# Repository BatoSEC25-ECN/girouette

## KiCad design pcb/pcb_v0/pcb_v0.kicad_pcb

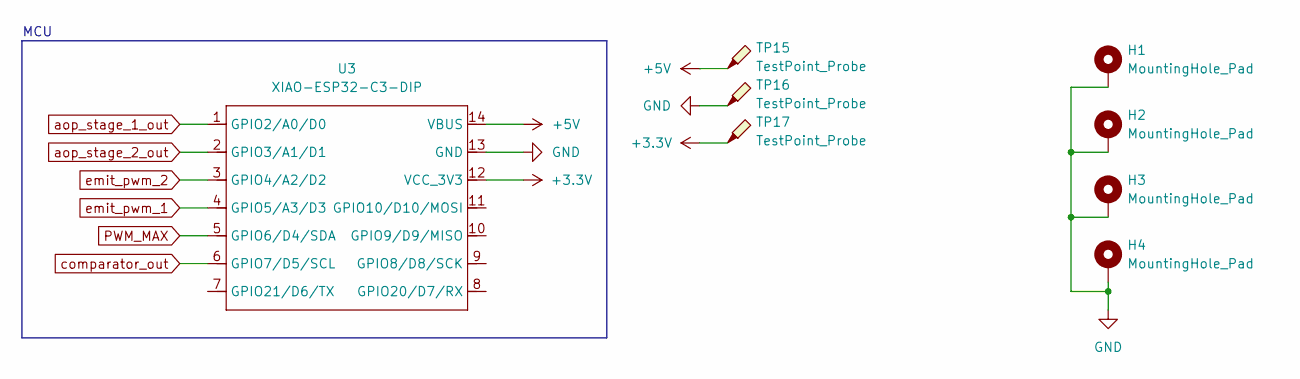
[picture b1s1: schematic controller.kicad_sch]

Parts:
H1, H2, H3, H4: MountingHole_Pad; MountingHole_2.2mm_M2_Pad_TopBottom
TP15, TP16, TP17: TestPoint_Probe; TestPoint_THTPad_3.0x3.0mm_Drill1.5mm
U3: XIAO-ESP32-C3-DIP; XIAO-ESP32C3-DIP

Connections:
+3.3V: TP17.1, U3.12 (VCC_3V3); also elsewhere on the board
+5V: TP15.1, U3.14 (VBUS); also elsewhere on the board
GND: H1.1, H2.1, H3.1, H4.1, TP16.1, U3.13 (GND); also elsewhere on the board
PWM_MAX: U3.5 (GPIO6/D4/SDA); also elsewhere on the board
aop_stage_1_out: U3.1 (GPIO2/A0/D0); also elsewhere on the board
aop_stage_2_out: U3.2 (GPIO3/A1/D1); also elsewhere on the board
comparator_out: U3.6 (GPIO7/D5/SCL); also elsewhere on the board
emit_pwm_1: U3.4 (GPIO5/A3/D3); also elsewhere on the board
emit_pwm_2: U3.3 (GPIO4/A2/D2); also elsewhere on the board

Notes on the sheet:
MCU

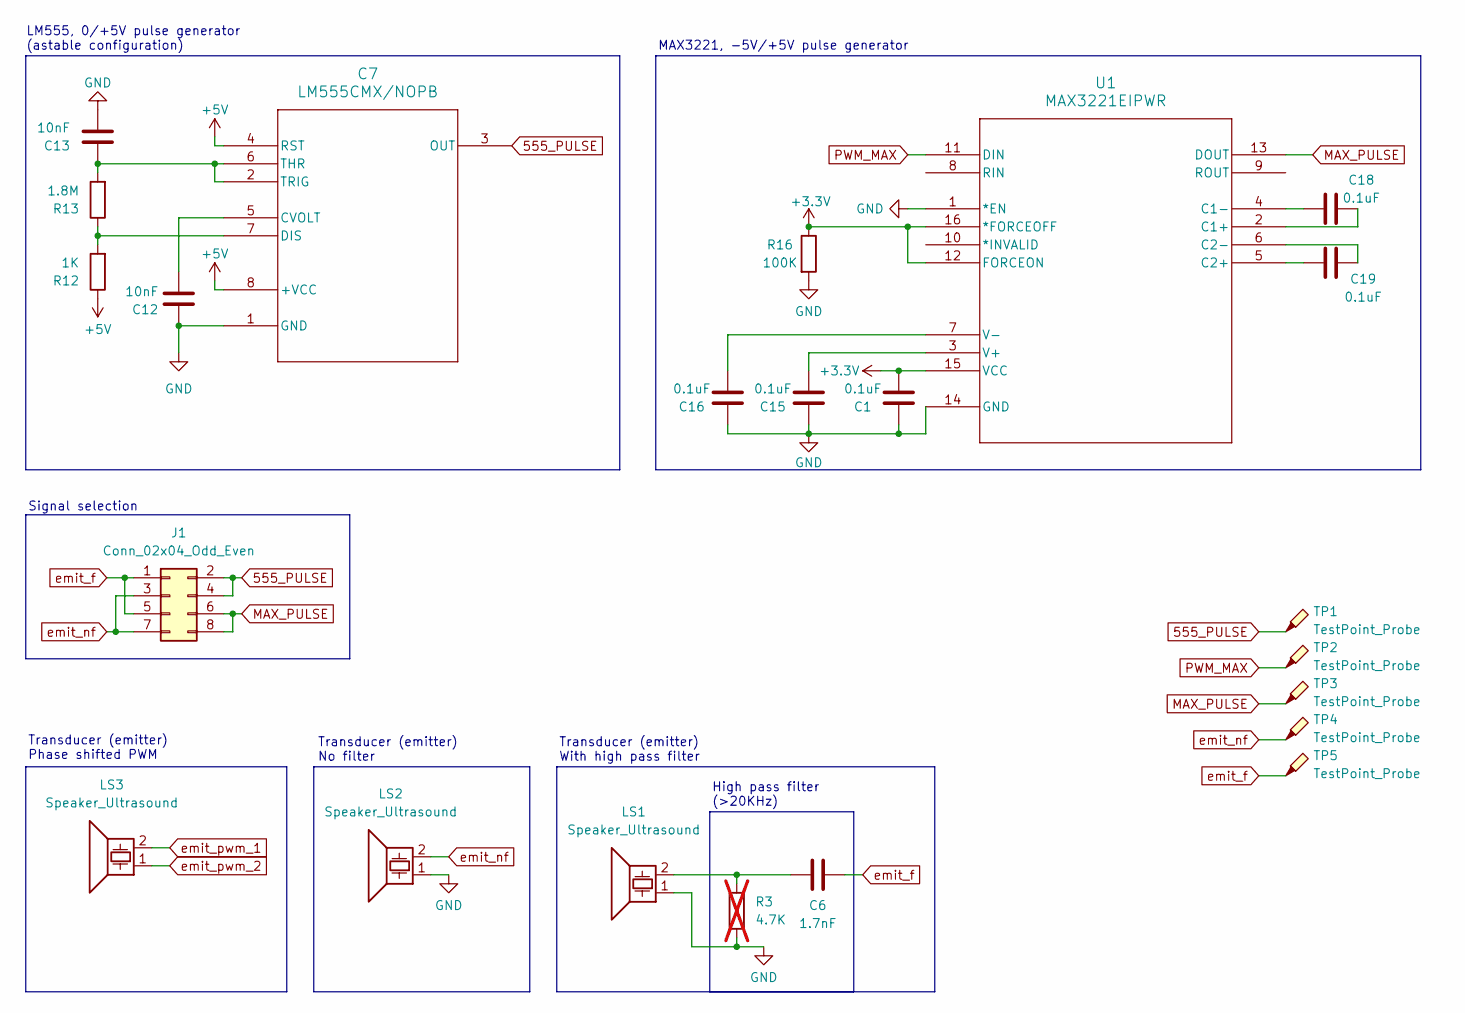
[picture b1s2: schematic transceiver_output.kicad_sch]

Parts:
C1, C15, C16, C18, C19: 0.1uF; C_Disc_D4.3mm_W1.9mm_P5.00mm
C6: 1.7nF; C_Disc_D4.3mm_W1.9mm_P5.00mm
C7: LM555CMX/NOPB; M08A-M
C12, C13: 10nF; C_Disc_D4.3mm_W1.9mm_P5.00mm
J1: Conn_02x04_Odd_Even; PinHeader_2x04_P2.54mm_Vertical
LS1, LS2, LS3: Speaker_Ultrasound; PinHeader_1x02_P2.54mm_Vertical
R3: 4.7K; R_Axial_DIN0207_L6.3mm_D2.5mm_P10.16mm_Horizontal; not fitted
R12: 1K; R_Axial_DIN0207_L6.3mm_D2.5mm_P10.16mm_Horizontal
R13: 1.8M; R_Axial_DIN0207_L6.3mm_D2.5mm_P10.16mm_Horizontal
R16: 100K; R_Axial_DIN0207_L6.3mm_D2.5mm_P10.16mm_Horizontal
TP1, TP2, TP3, TP4, TP5: TestPoint_Probe; TestPoint_THTPad_3.0x3.0mm_Drill1.5mm
U1: MAX3221EIPWR; PW16-M

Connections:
555_PULSE: C7.3 (OUT), J1.2, J1.4, TP1.1
+3.3V: C1.2, R16.1, U1.12 (FORCEON), U1.15 (VCC), U1.16 (*FORCEOFF); also elsewhere on the board
+5V: C7.4 (RST), C7.8 (+VCC), R12.1; also elsewhere on the board
GND: C1.1, C7.1 (GND), C12.1, C13.2, C15.1, C16.1, LS1.1, LS2.1, R3.2, R16.2, U1.1 (*EN), U1.14 (GND); also elsewhere on the board
MAX_PULSE: J1.6, J1.8, TP3.1, U1.13 (DOUT)
unnamed: C6.1, LS1.2, R3.1
unnamed: C7.5 (CVOLT), C12.2
unnamed: C7.7 (DIS), R12.2, R13.1
unnamed: C7.2 (TRIG), C7.6 (THR), C13.1, R13.2
unnamed: C18.2, U1.2 (C1+)
unnamed: C18.1, U1.4 (C1-)
unnamed: C19.1, U1.5 (C2+)
unnamed: C19.2, U1.6 (C2-)
unnamed: C15.2, U1.3 (V+)
unnamed: C16.2, U1.7 (V-)
PWM_MAX: TP2.1, U1.11 (DIN); also elsewhere on the board
emit_f: C6.2, J1.1, J1.5, TP5.1
emit_nf: J1.3, J1.7, LS2.2, TP4.1
emit_pwm_1: LS3.2; also elsewhere on the board
emit_pwm_2: LS3.1; also elsewhere on the board

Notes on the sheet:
Transducer (emitter) No filter
Signal selection
LM555, 0/+5V pulse generator (astable configuration)
MAX3221, -5V/+5V pulse generator
High pass filter (>20KHz)
Transducer (emitter) Phase shifted PWM
Transducer (emitter) With high pass filter

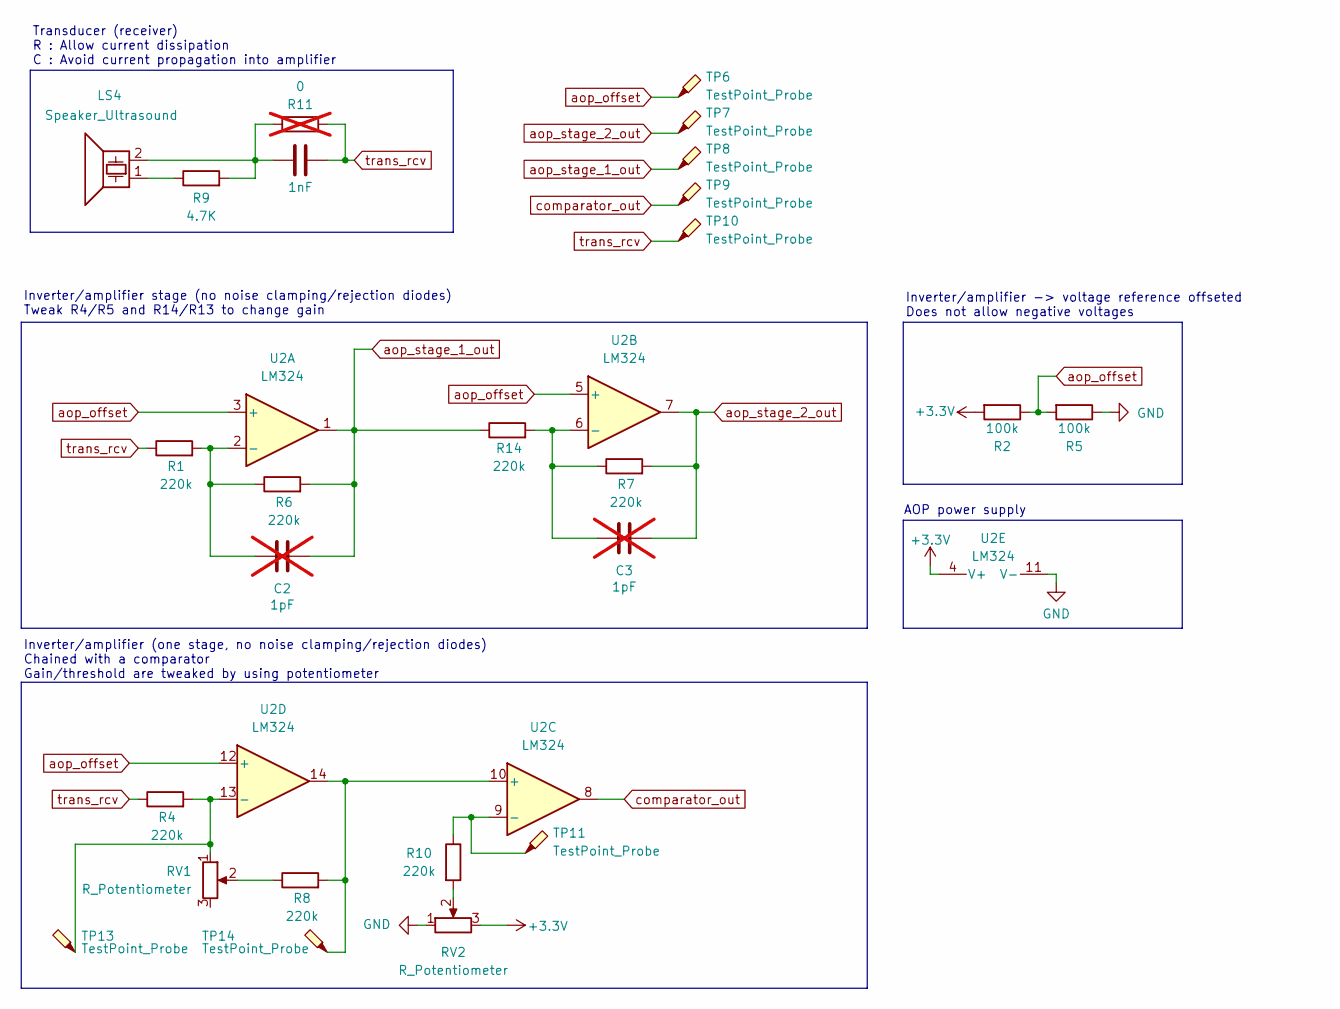
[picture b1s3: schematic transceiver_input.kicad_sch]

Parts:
C2, C3: 1pF; C_Disc_D4.3mm_W1.9mm_P5.00mm; not fitted
C10: 1nF; C_Disc_D4.3mm_W1.9mm_P5.00mm
LS4: Speaker_Ultrasound; PinHeader_1x02_P2.54mm_Vertical
R1, R4, R6, R7, R8, R10, R14: 220k; R_Axial_DIN0207_L6.3mm_D2.5mm_P10.16mm_Horizontal
R2, R5: 100k; R_Axial_DIN0207_L6.3mm_D2.5mm_P10.16mm_Horizontal
R9: 4.7K; R_Axial_DIN0207_L6.3mm_D2.5mm_P10.16mm_Horizontal
R11: 0; R_Axial_DIN0207_L6.3mm_D2.5mm_P10.16mm_Horizontal; not fitted
RV1, RV2: R_Potentiometer; Potentiometer_Bourns_PTV09A-1_Single_Vertical
TP6, TP7, TP8, TP9, TP10, TP11, TP13, TP14: TestPoint_Probe; TestPoint_THTPad_3.0x3.0mm_Drill1.5mm
U2: LM324; N14

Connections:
+3.3V: R2.2, RV2.3, U2.4 (V+); also elsewhere on the board
GND: R5.1, RV2.1, U2.11 (V-); also elsewhere on the board
unnamed: C10.1, LS4.2, R9.2, R11.2
unnamed: LS4.1, R9.1
unnamed: R8.1, RV1.2
unnamed: R10.2, RV2.2
unnamed: C2.2, R1.2, R6.1, U2.2 (-)
unnamed: C3.2, R7.1, R14.2, U2.6 (-)
unnamed: R8.2, TP14.1, U2.10 (+), U2.14
unnamed: R10.1, TP11.1, U2.9 (-)
unnamed: R4.2, RV1.1, TP13.1, U2.13 (-)
aop_offset: R2.1, R5.2, TP6.1, U2.3 (+), U2.5 (+), U2.12 (+)
aop_stage_1_out: C2.1, R6.2, R14.1, TP8.1, U2.1; also elsewhere on the board
aop_stage_2_out: C3.1, R7.2, TP7.1, U2.7; also elsewhere on the board
comparator_out: TP9.1, U2.8; also elsewhere on the board
trans_rcv: C10.2, R1.1, R4.1, R11.1, TP10.1

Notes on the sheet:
Inverter/amplifier -> voltage reference offseted Does not allow negative voltages
Inverter/amplifier (one stage, no noise clamping/rejection diodes) Chained with a comparator Gain/threshold are tweaked by using potentiometer
AOP power supply
Inverter/amplifier stage (no noise clamping/rejection diodes) Tweak R4/R5 and R14/R13 to change gain
Transducer (receiver) R : Allow current dissipation C : Avoid current propagation into amplifier

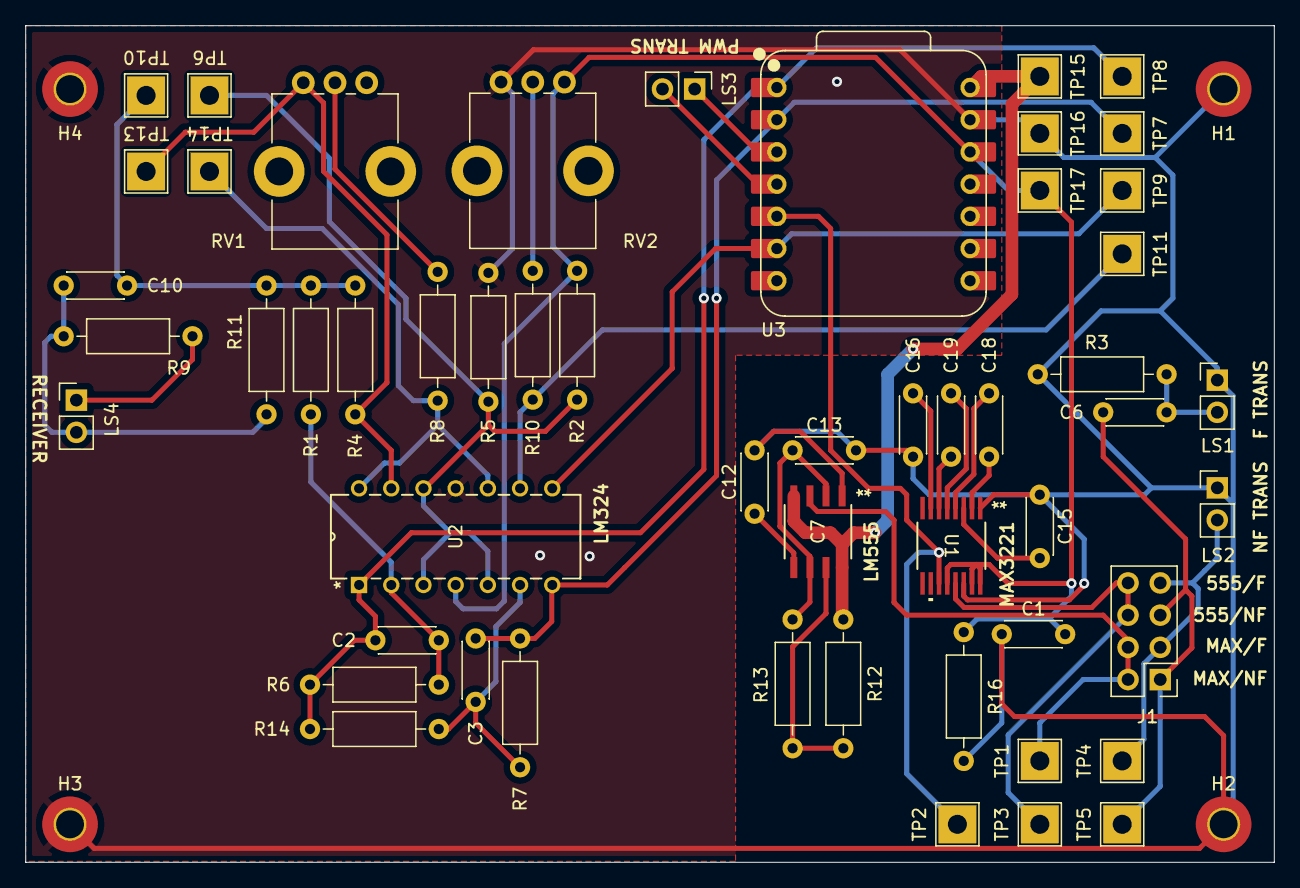
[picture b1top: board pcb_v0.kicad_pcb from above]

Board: 2 copper layers, 98.5 x 66.0 mm, 57 parts (0 on the bottom side), 34 nets.

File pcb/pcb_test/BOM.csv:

"Id";"Designator";"Footprint";"Quantity";"Designation";"Supplier and ref";
1;"C10";"C_Disc_D3.0mm_W1.6mm_P2.50mm";1;"1nF";;;
2;"TP2,TP14,TP6,TP10,TP15,TP8,TP17,TP3,TP13,TP4,TP7,TP1,TP9,TP16,TP5,TP11";"TestPoint_THTPad_1.0x1.0mm_Drill0.5mm";16;"TestPoint_Probe";;;
3;"R5,R2";"R_Axial_DIN0204_L3.6mm_D1.6mm_P5.08mm_Horizontal";2;"100k";;;
4;"C12,C13";"C_Disc_D3.0mm_W1.6mm_P2.50mm";2;"10nF";;;
5;"R10,R8,R14,R4,R7,R6,R1";"R_Axial_DIN0204_L3.6mm_D1.6mm_P5.08mm_Horizontal";7;"220k";;;
6;"LS2,LS1,LS3,LS4";"PinHeader_1x02_P2.54mm_Vertical";4;"Speaker_Ultrasound";;;
7;"C16,C19,C18,C15,C1";"C_Disc_D3.0mm_W1.6mm_P2.50mm";5;"0.1uF";;;
8;"U3";"XIAO-ESP32C3-DIP";1;"XIAO-ESP32-C3-DIP";;;
9;"C3,C2";"C_Disc_D3.0mm_W1.6mm_P2.50mm";2;"1pF";;;
10;"R3,R9";"R_Axial_DIN0204_L3.6mm_D1.6mm_P5.08mm_Horizontal";2;"4.7K";;;
11;"R12";"R_Axial_DIN0204_L3.6mm_D1.6mm_P5.08mm_Horizontal";1;"1K";;;
12;"J1,J4,J2,J3";"PinHeader_1x02_P2.54mm_Vertical";4;"Conn_01x02_Pin";;;
13;"C6";"C_Disc_D3.0mm_W1.6mm_P2.50mm";1;"1.7nF";;;
14;"U1";"PW16-M";1;"MAX3221EIPWR";;;
15;"C7";"M08A-M";1;"LM555CMX/NOPB";;;
16;"R16";"R_Axial_DIN0204_L3.6mm_D1.6mm_P5.08mm_Horizontal";1;"100K";;;
17;"RV1,RV2";"Potentiometer_Bourns_PTV09A-1_Single_Vertical";2;"R_Potentiometer";;;
18;"R13";"R_Axial_DIN0204_L3.6mm_D1.6mm_P5.08mm_Horizontal";1;"1.8M";;;
19;"U2";"DIP-14_W7.62mm_Socket_LongPads";1;"LM324";;;

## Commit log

2024-12-12 Add multi language .gitignore
2024-12-12 Create doc
2025-01-17 Add PEP documentat
2025-02-15 chore(gitignore): update gitignore
2025-02-15 feat(pcb_v0): Create first pcb version (v0, for test purpose)"
2025-02-15 chore(prod_files): add production generated files
2025-02-15 chore: Add BOM file
2025-03-11 chore(order): update order list
2025-03-11 fix(pcb): update design to match teacher requirements
2025-03-11 fix(pcb): update footprints to solve ERC issues
2025-03-15 doc: add components datasheet
2025-03-15 fix(pcb_v0): Update resistor and capacitor values
2025-03-15 feat!(3D): Add 3D printer (3mf) and Fusion 360 (f3z) files.
2025-03-15 fix: clean project
    - Remove duplicated components datasheet
    - Remove duplicated production files (old version, never ordered)
2025-03-15 fix: Update gitignore for kicad and openoffice
2025-03-15 doc: Add components ref for future pcb
2025-03-15 doc: Add code setup documentation
2025-03-15 fix: update .gitignore for esp-idf files
2025-03-15 feat!: Add esp32 C3 blink code template.
2025-03-21 fix: add modeling files and rename some
2025-03-21 refactor: rename all files
2025-03-21 fix: patch psb test issues and delete generated files
2025-03-21 fix: patch 3d models
2025-03-25 fix: update code
2025-03-25 fix: update CAD models
2025-03-25 fix: patch pcb design
2025-03-25 doc: update documentation
2025-03-25 fix: restore code to empty project
2025-03-26 Revert "Pcb test"
2025-03-26 Pcb test (#4)
    * chore(gitignore): update gitignore
    * feat(pcb_v0): Create first pcb version (v0, for test purpose)"
    * chore(prod_files): add production generated files
    * chore: Add BOM file
    * fix(pcb): update design to match teacher requirements
    * fix(pcb): update footprints to solve ERC issues
2025-03-26 doc: update documentation and patch typo
2025-03-26 fix: update uncrustify configuration file
2025-03-26 Gdm doc patch (#5)
    * doc: update documentation and patch typo
    * fix: update uncrustify configuration file
2025-03-26 doc: add fusion360 download page
2025-03-28 chore: update gitignore and provided tools
2025-03-28 Add documentation
2025-05-19 feat!: create MCU pwm burst generation
2025-05-19 feat!: add keysight custom library and required dataclasses
2025-05-19 chore: update gitignore and required tools
2025-05-19 doc: improve setup documentation
2025-05-19 chore: add python libraries requirements
2025-05-19 doc: add keysight developper datasheet
2025-05-19 feat: create a plotter to compare two data curve
2025-05-19 refactor: update main to match previous changes
2025-05-19 feat!: add possibility of running multiple tests
    Add multiple features to run "infinite" amount of tests:
    - plotter handles an undefined amount of .csv files from a list (restr
    icted to 5 colors though, curves color could overlap)
    - keysight file formatting is standardized (lower case, ensure .csv at
    the end, replace spaces with underscore)
    - main is updated to run an undefined amount of measurement, prompting
2025-05-19 refactor(plotter): improve readability and split some functions logic
2025-05-19 fix: remove uncrustify config (duplicated, wrong folder)
2025-05-19 feat: add a logger for debug purpose
2025-05-19 refactor(dataclasses): improve readability and split some functions logic
2025-05-19 refactor: remove unused dependencies
2025-05-19 refactor(keysight): improve readability and split some functions logic
2025-05-19 feat!: create main runner script
2025-05-24 fix:clean probe ratio
    D:\Documents\41_Ecole\4_Centrale_Nantes\A3\_Projet_bateau\girouette\code\measure_tool\main.py
2025-05-25 refactor(dataclasses): refactor code
    D:\Documents\41_Ecole\4_Centrale_Nantes\A3\_Projet_bateau\girouette\code\measure_tool\dataclass.py
2025-05-25 feat: reimplement probe ratio
    D:\Documents\41_Ecole\4_Centrale_Nantes\A3\_Projet_bateau\girouette\code\measure_tool\dataclass.pyD:\Documents\41_Ecole\4_Centrale_Nantes\A3\_Projet_bateau\girouette\code\measure_tool\keysight.py
2025-05-25 refactor(keysight): refactor code
2025-06-25 fix: patch frequency clamping
2025-06-25 feat: add horizontal markers
2025-06-25 fix: fix plotter issues
    D:\Documents\41_Ecole\4_Centrale_Nantes\A3\_Projet_bateau\girouette\code\measure_tool\plotter.py
2025-06-25 close project
2025-06-25 Measurement tools and minors patches (#6)
    * doc: add fusion360 download page
    * chore: update gitignore and required tools
    * doc: add keysight developper datasheet
    * doc: improve setup documentation
    * chore: add python libraries requirements
    * feat!: create MCU pwm burst generation
2025-08-08 feat: add fusion360 rotating test bench
2025-08-08 feat: add demos
